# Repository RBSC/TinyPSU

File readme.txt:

--------------------------------------------------------------------------------
Tiny Power Supply for MSX Computers
Copyright (c) 2024-2025 RBSC
Last updated: 13.07.2025
--------------------------------------------------------------------------------

About
-----

This project was created by Wierzbowsky [RBSC] and Ptero [RBSC] in order to bring back to life a batch of MSX2 computers,
mostly Panasonic FS-A1. Those computers were lacking original power supply units that made them unusable. It's a known fact
that original power supplies for those computers are hard to come by and even if one is lucky to find one for sale, the
price literally bites. Japanese sellers may easily ask for 70$ for such a power supply. Overseas shipment, local and import
taxes can easily bring the total cost of the power supply to 100$. But that's not the only problem.

The second problem is that these MSX2 computers have the special 3-pin power socket that was not used in many other MSX
computers. So, reusing power supplies from other MSX computers was not an option. However, similar sockets were used in
some old laptops, so it possible to find an old laptop power supply in order to utilize its cable to build a custom power
supply for Panasonic FS-A1 or FS-A1 MK2 computers.

But the usage of this power supply is not only limited to Panasonic FS-A1 and similar computers. Technically, this power
supply can be used in any MSX computer that requires 3 different voltages: +5V, +12V and -12V. This repository contains the
holder for the Tiny PSU that could be used with Yamaha YIS 503II, 503III, CX5M, CX11 and similar MSX and MSX2 computers.
There's no need to even modify the motherboard in order to fit this power supply into those computers.

There's the special document-guide in the Docs subfolder of this repository that provides precise instructions on how to
build the Tiny PSU in. Please carefully read the "FS-A1_FS-A1MK2_PSU_Guide.pdf" document before doing any repair!

Building in the PSU
-------------------

For certain computers, for example for Yamaha MSX YIS-503 and similar computers, the installation of the Tiny PSU is almost
trivial. The PSU needs to be fitted with the power connector similar to the original one (or even the original connector can
be used instead). The installation of the Tiny PSU into Panasonic FS-A1 and FS-A1MK2 computers is a totally different thing.
To make space for the Tiny PSU certain components must be removed from the mainboard and some additional modifications must
be made to complete the PSU replacement. See the specially created guide document to help you during the installation.

Before starting the repair or upgrade please make sure that you have sufficient skills and all necessary tools. For example,
desoldering components from old circuit boards must be done with extreme caution in order not to damage the main circuit
board. Proper soldering skills are needed to correctly connect the Tiny PSU to the mainboard. In addition, you may need
crimping tools, connector shells, crimps and cable insulation stripping tools. If you feel that you don't have enough skills
and tools, leave the work to better equipped people.

As mentioned above, there's a possibility to built the Tiny PSU into almost any MSX computer. But every computer may have
its differences, so the installation into each computer or into a family of computers (like Yamaha YIS 503) may require
a different approach. The available 3D models of Tiny PSU's holders could be adjusted to be used in other computer models.
If in doubt, seek a piece of advice on MSX.ORG and other forums about vintage electonics.

Where else to find 3D models of Tiny PSU's holders:

 - For Panasonic: https://www.thingiverse.com/thing:6987948
 - For Yamaha: https://www.thingiverse.com/thing:6847546

Tiny PSU Assembling Notes
-------------------------

Please read the following notes carefully:

 - Use only recommended fuse values for the Tinu PSU. Incorrect fuse value may result in a damage to a computer or external
   power supply

 - Use only the recommended external 9V or 12V power supply. Other PSUs, especially cheap ones from AliExpress may result
   in a malfunction of the Tiny PSU and/or introduce interference into the audio and video signals of a computer. See the
   installation guide document for the info about the recommened external power supply

 - Use only recommended voltage ratings for electrolytic capacitors. Incorrect voltage rating may result in blown or leaked
   capacitors and other anomalies

 - Use only recommended suppressor diode with breakdown voltages from 5.6V up to 6.4V. Higher or lover breakdown voltages
   may result in a non-working power supply or may damage your MSX computer!

 - Use only the recommended coil types and coil values. Incorrect coil type or its value may result in severe pulsation
   on the power rails that may prevent a computer from operating properly

 - When selecting wires for connecting the Tiny PSU to the mainboard, please make sure that they can hold up to 2A current,
   otherwise your computer may be starving for power if too thin or low quality wires are used

 - The ST1S10 step-down voltage regulator IC may get hot during its operation. The lead frame die pad of the ST1S10 is
   exposed at the bottom of the package and must be soldered directly to a properly designed thermal pad on the PCB. This
   means that soldering must be done either with hot air from the reworking station or with the help of the infrared
   reworking station that heats the board from the bottom. The heat from the IC will be dissipated via the carefully
   designed thermal pad

 - The XL6007E1 DC-DC convertor IC may get hot during its operation. Unlike the ST1S10, it doesn't have a die pad on the
   bottom to be soldered onto the board. So, it's recommended to apply good thermal paste onto the bottom of the IC before
   soldering its 8 pins to the circuit board

 - While the +12V circuit was designed for up to 2A load, the total -12V circuit's load must not exceed 100mA. Most of MSX
   computers and cartridges will not exceed this load during normal operation. This limitation comes from the VA-1212S 1W
   DC-DC converter that is installed to produce -12V for the MSX power rail

 - Though the circuit board is designed to dissipate the heat from active elements, it's not recommended to install the
   Tiny PSU in poorly ventilated tight spaces, as well as near other sources of heat. The step-down converter may heat up
   to 60 degrees Celsius, the -12V DC-DC converter may heat up slightly more. During the testing phase the Tiny PSU was
   tested for many hours with the maxumum allowed load with constant temperature monitoring and no excessive heating has
   been observed

IMPORTANT!
----------

The RBSC provides all the files and information for free, without any liability (see the disclaimer.txt file). The provided
information, software or hardware must not be used for commercial purposes unless permitted by the RBSC. Producing a small
amount of bare boards for personal projects and selling the rest of the batch is allowed without the permission of RBSC.

When the sources of the tools are used to create alternative projects, please always mention the original source and the
copyright!

Contact information
-------------------

The members of RBSC group Tnt23, Wierzbowsky, Pyhesty, Ptero, GreyWolf, SuperMax, VWarlock, ALSP and DJS3000 can be contacted
via the group's e-mail address:

info@rbsc.su

The group's coordinator could be reached via this e-mail address:

admin@rbsc.su

The group's website can be found here:

https://rbsc.su/
https://rbsc.su/ru

The RBSC's hardware repository can be found here:

https://github.com/rbsc

The RBSC's 3D model repository can be found here:

https://www.thingiverse.com/groups/rbsc/things

-= ! MSX FOREVER ! =-

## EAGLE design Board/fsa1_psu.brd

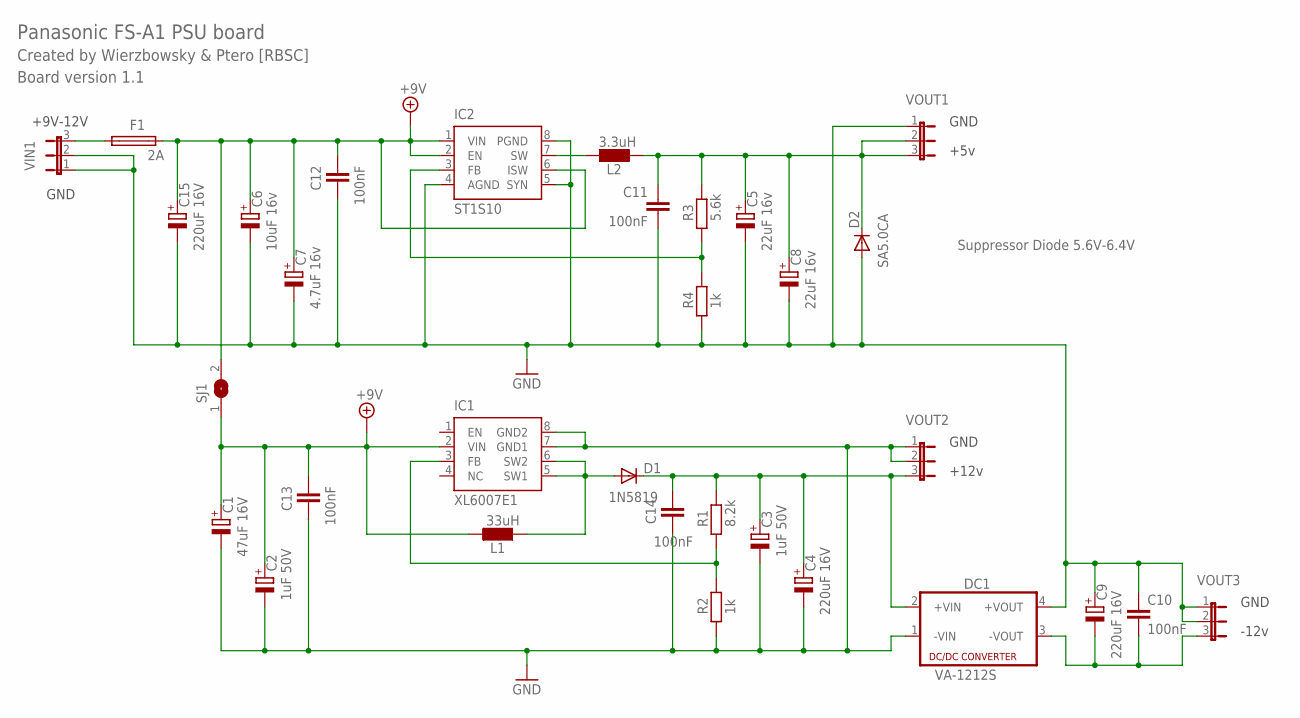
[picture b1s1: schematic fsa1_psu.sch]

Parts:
C1: 47uF 16V; SANYO-OSCON_C6
C2, C3: 1uF 50V; SANYO-OSCON_C6
C4, C9, C15: 220uF 16V; SANYO-OSCON_E7
C5, C8: 22uF 16v; SANYO-OSCON_C6
C6: 10uF 16v; SANYO-OSCON_C6
C7: 4.7uF 16v; SANYO-OSCON_C6
C10, C11, C12, C13, C14: 100nF; C0805
D1: 1N5819; DO204-10
D2: SA5.0CA; DO204-10
DC1: VA-1212S; 4SIL
F1: 2A; PICOFUSE
IC1: XL6007E1; SOIC08
IC2: ST1S10; SOIC08
L1: 33uH; 0204/7
L2: 3.3uH; 0204/7
R1: 8.2k; 0204/7
R2, R4: 1k; 0204/7
R3: 5.6k; 0204/7
SJ1: SJ
VIN1: JP2E_SP; JP2
VOUT1, VOUT2, VOUT3: JP2E_SP; JP2

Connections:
5VOUT: C5.+, C8.+, C11.1, D2.C, L2.2, R3.2, VOUT1.2, VOUT1.3
+9V: C1.+, C2.+, C6.+, C7.+, C12.1, C13.1, C15.+, F1.2, IC1.2 (VIN), IC2.1 (VIN), IC2.2 (EN), IC2.6 (ISW), L1.1, SJ1.1, SJ1.2
+12VOUT: C3.+, C4.+, C14.1, D1.C, DC1.2 (+VIN), R1.2, VOUT2.3
EXTHOLE3: D1.A, IC1.5 (SW1), IC1.6 (SW2), L1.2
GND: C1.-, C2.-, C3.-, C4.-, C5.-, C6.-, C7.-, C8.-, C9.+, C10.1, C11.2, C12.2, C13.2, C14.2, C15.-, D2.A, DC1.1 (-VIN), DC1.4 (+VOUT), IC1.7 (GND1), IC1.8 (GND2), IC2.4 (AGND), IC2.5 (SYN), IC2.8 (PGND), R2.1, R4.1, VIN1.1, VIN1.2, VOUT1.1, VOUT2.1, VOUT2.2, VOUT3.1, VOUT3.2
unnamed: IC2.7 (SW), L2.1
unnamed: F1.1, VIN1.3
unnamed: IC1.3 (FB), R1.1, R2.2
unnamed: IC2.3 (FB), R3.1, R4.2
unnamed: C9.-, C10.2, DC1.3 (-VOUT), VOUT3.3

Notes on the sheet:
Panasonic FS-A1 PSU board
Created by Wierzbowsky & Ptero [RBSC]
Board version 1.1
-12v
+12v
+5v
GND
+9V-12V
Suppressor Diode 5.6V-6.4V

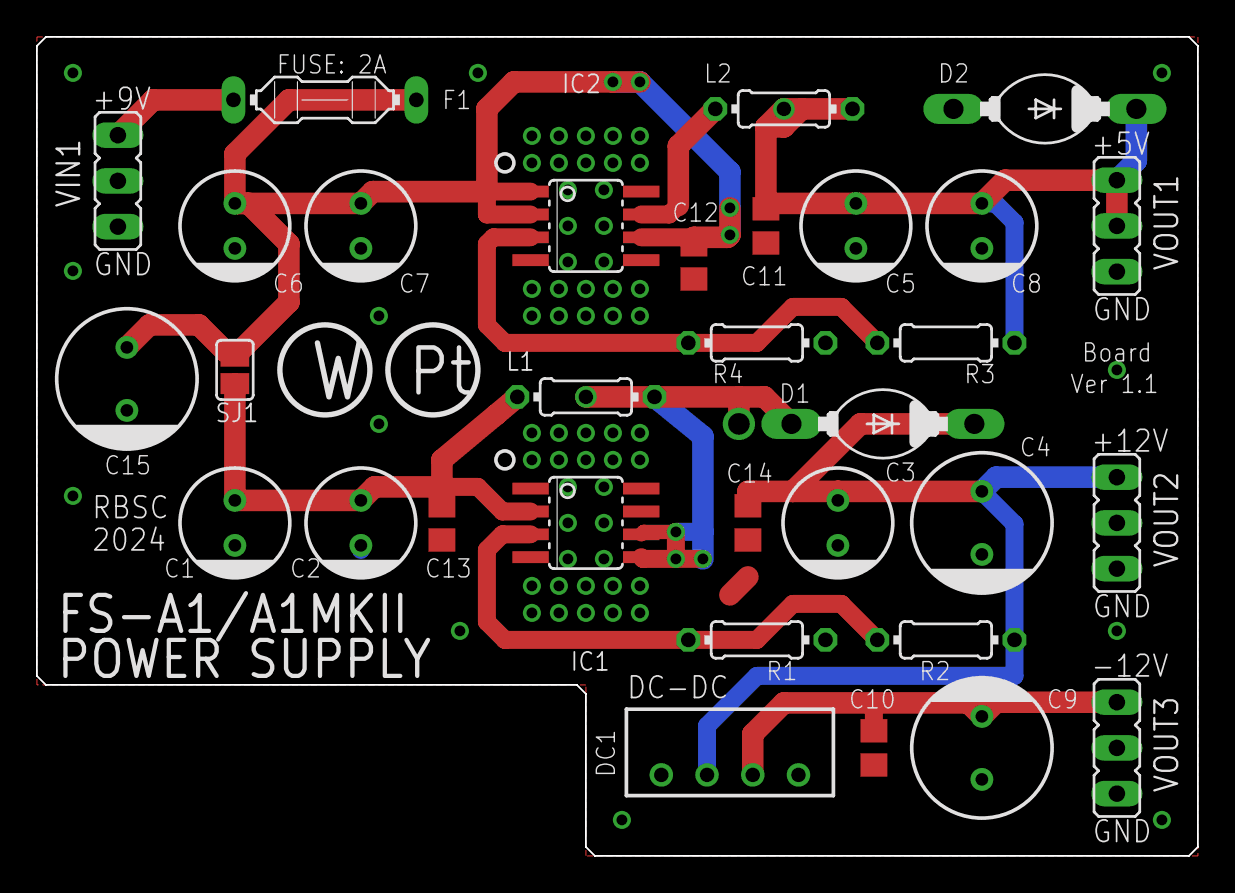
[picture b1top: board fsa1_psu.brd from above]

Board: 2 copper layers, 64.5 x 45.5 mm, 32 parts (0 on the bottom side), 10 nets.

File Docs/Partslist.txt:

Partlist

Part     Value          Device          Package        Library         Sheet
----------------------------------------------------------------------------
C1       47uF 16V       CPOL-EUSANYO_C6 SANYO-OSCON_C6 rcl             1
C2       1uF 50V        CPOL-EUSANYO_C6 SANYO-OSCON_C6 rcl             1
C3       1uF 50V        CPOL-EUSANYO_C6 SANYO-OSCON_C6 rcl             1
C4       220uF 16V      CPOL-EUSANYO_E7 SANYO-OSCON_E7 rcl             1
C5       22uF 16v       CPOL-EUSANYO_C6 SANYO-OSCON_C6 rcl             1
C6       10uF 16v       CPOL-EUSANYO_C6 SANYO-OSCON_C6 rcl             1
C7       4.7uF 16v      CPOL-EUSANYO_C6 SANYO-OSCON_C6 rcl             1
C8       22uF 16v       CPOL-EUSANYO_C6 SANYO-OSCON_C6 rcl             1
C9       220uF 16V      CPOL-EUSANYO_E7 SANYO-OSCON_E7 rcl             1
C10      100nF          C-EUC0805       C0805          rcl             1
C11      100nF          C-EUC0805       C0805          rcl             1
C12      100nF          C-EUC0805       C0805          rcl             1
C13      100nF          C-EUC0805       C0805          rcl             1
C14      100nF          C-EUC0805       C0805          rcl             1
C15      220uF 16V      CPOL-EUSANYO_E7 SANYO-OSCON_E7 rcl             1
D1       1N5819         DIODE-DO204-10  DO204-10       diode           1
D2       SA5.0CA        DIODE-DO204-10  DO204-10       diode           1
DC1      VA-1212S       VA-1212S        4SIL           dc-dc-converter 1
F1       3A             PICOFUSE        PICOFUSE       fuse            1
IC1      XL6007E1       XL6007E1-SOIC   SOIC08         XL6007E1        1
IC2      ST1S10         ST1S10-SOIC     SOIC08         ST1S10          1
L1       33uH           L0204/7         0204/7         eagle-ltspice   1
L2       3.3uH          L0204/7         0204/7         eagle-ltspice   1
R1       8.2k           R-EU_0204/7     0204/7         resistor        1
R2       1k             R-EU_0204/7     0204/7         resistor        1
R3       5.6k           R-EU_0204/7     0204/7         resistor        1
R4       1k             R-EU_0204/7     0204/7         resistor        1
VIN1                    JP2E_SP         JP2            wire_clamp      1
VOUT1                   JP2E_SP         JP2            wire_clamp      1
VOUT2                   JP2E_SP         JP2            wire_clamp      1
VOUT3                   JP2E_SP         JP2            wire_clamp      1

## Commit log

2025-07-13 Initial release 13.07.2025
    Initial release of project's files and installation guide
2025-07-13 Initial release 13.07.2025
    Initial release of the project files and installation guide
2025-07-14 Updated 14.07.2025
    Updated the installation guide document
